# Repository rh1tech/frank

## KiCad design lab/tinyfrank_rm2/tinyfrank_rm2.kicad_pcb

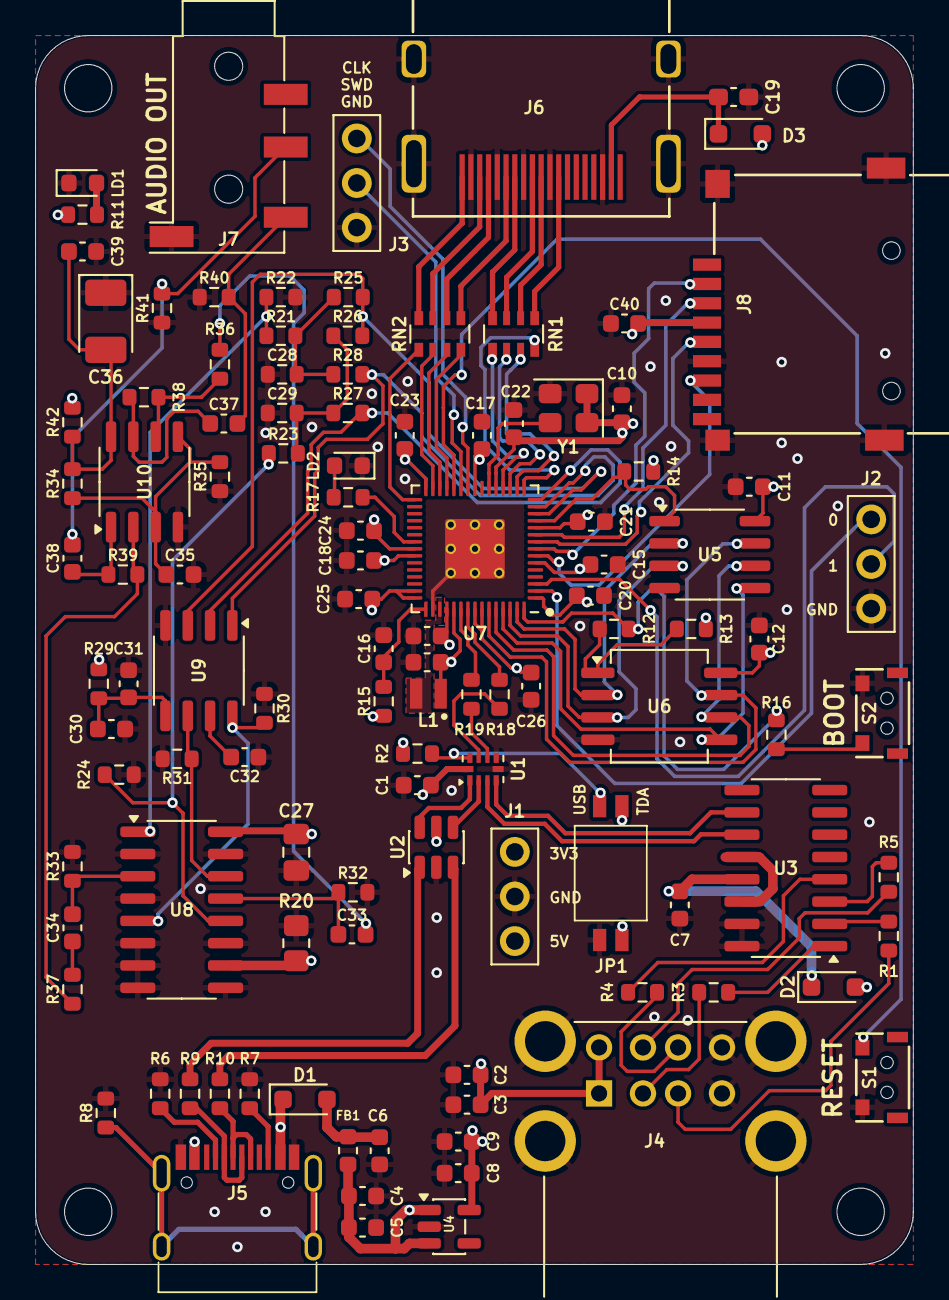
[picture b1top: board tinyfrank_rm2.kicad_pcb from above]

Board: 4 copper layers, 50.0 x 70.0 mm, 117 parts (0 on the bottom side), 97 nets.

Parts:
C1, C5, C6, C8, C10, C11, C12, C15, C18, C20, C21, C22, C23, C24, C25, C26, C31, C39, C40: 100n; C_0603_1608Metric
C2, C3, C4, C9, C30, C32, C33, C34, C35, C37, C38: 10u; C_0603_1608Metric
C7, C13, C14, C16, C17: 4.7u; C_0603_1608Metric
C19: 100n; Capacitor (0603)
C27: 100n; Capacitor (0805)
C28, C29: 47n; R_0603_1608Metric
C36: 10u; Capacitor (3528, tantalum, polar)
D1, D2, D3: 1N5819WS; Diode (SOD-323)
FB1: 330R; L_0603_1608Metric
H1, H2, H3, H4: Hole 2.7mm; Mounting Hole (2.7mm)
J1: PWR; Pin Header (1x03)
J2: UART; Pin Header (1x03)
J3: DEBUG; Pin Header (1x03)
J4: SS-52100-004; USB Type A (stacked)
J5: USB4215-03-A; USB Type C
J6: DC3RX19JA2; HDMI (female)
J7: PJ-320D; Jack (3.5mm, PJ-320D)
J8: 104031-0811; MicroSD (SMD, long)
JP1: Main Jumpers; DS05127202BKSMTTR
L1: 3.3u; L_pol_2016
LD1: Green; LED_0603_1608Metric
LD2: Blue; LED_0603_1608Metric
R1, R3, R4, R5, R9, R10: 22R; R_0603_1608Metric
R2, R13, R14, R21, R23, R32, R33, R34, R35, R36, R37: 10K; R_0603_1608Metric
R6, R7: 5.1K; R_0603_1608Metric
R8: 1M; R_0603_1608Metric
R11, R16, R17, R27, R28: 1K; R_0603_1608Metric
R12: 0R; R_0603_1608Metric
R15: 33R; R_0603_1608Metric
R18, R19: 27R; R_0603_1608Metric
R20: 10K; Resistor (0805)
R22, R24, R25, R26: 2K; R_0603_1608Metric
R29, R42: 100R; R_0603_1608Metric
R30, R31: 470R; R_0603_1608Metric
R38, R39: 47K; R_0603_1608Metric
R40, R41: 20K; R_0603_1608Metric
RN1, RN2: 270R; Resistor Array (4x0603)
S1: Reset RP2530A; TACT-SIDE-4623
S2: TS-1233; TACT-SIDE-4623
U1: TS3USB221RSER; UQFN-10
U2: USBLC6-2SC6; SOT-23-6
U3: MW7211A; SOP-16
U4: ME6211C33M5; SOT-23-5
U5: ESP-PSRAM32; SO-8
U6: W25Q128JVS; SOIC-8
U7: RP2350; QFN 60 (RP2350A)
U8: 74HC4052D; SOP-16
U9: TDA1387T; SO-8
U10: LM358; SO-8
Y1: ASE-12MHz; Oscillator_SMD_Abracon_ASE-4Pin_3.2x2.5mm

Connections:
+1V1: C14.1, C15.1, C17.1, C18.1, L1.1, U7.6 (DVDD), U7.23 (DVDD), U7.39 (DVDD), U7.50 (VREG_FB)
+3V3: C1.2, C8.1, C9.1, C10.1, C11.1, C12.1, C13.1, C20.1, C21.1, C22.1, C23.1, C24.1, C25.1, C26.1, C27.2, C40.2, J1.1, J8.4 (VDD), R2.1, R11.2, R13.1, R14.2, R15.1, U1.10 (VCC), U4.5 (V_{OUT}), U5.8 (VCC), U6.8 (VCC), U7.1 (IOVDD), U7.11 (IOVDD), U7.20 (IOVDD), U7.30 (IOVDD), U7.38 (IOVDD), U7.44 (ADC_AVDD), U7.45 (IOVDD), U7.49 (VREG_VIN), U7.53 (USB_OTP_VDD), U7.54 (QSPI_IOVDD), U8.16 (VCC), Y1.1 (EN), Y1.4 (Vdd)
/AMP_L: C33.1, R32.1, U8.13 (1Z)
/AMP_OUT_L: C37.2, J7.T, R40.2
/AMP_OUT_R: C38.2, J7.R, R41.2
/AMP_R: C34.1, R33.1, U8.3 (2Z)
/AUDIOSW: JP1.1, R20.2, U8.10 (S0)
/D+: R18.1, U1.8 (D+)
/D-: R19.1, U1.7 (D-)
/GPIO0: J2.1, U7.2 (GPIO0)
/GPIO1: J2.2, U7.3 (GPIO1)
/GPIO4: J8.7 (DAT0), U7.7 (GPIO4)
/GPIO5: J8.2 (DAT3/CD), U7.8 (GPIO5)
/GPIO6: J8.5 (CLK), U7.9 (GPIO6)
/GPIO7: J8.3 (CMD), U7.10 (GPIO7)
/GPIO8: R14.1, U5.1 (~CE), U7.12 (GPIO8)
/GPIO9: R25.1, R26.1, U7.13 (GPIO9), U9.3 (DATA)
/GPIO10: R28.2, U7.14 (GPIO10), U9.1 (SCLK)
/GPIO11: R27.2, U7.15 (GPIO11), U9.2 (LRCK)
/GPIO12: RN1.4 (R4.1), U7.16 (GPIO12)
/GPIO13: RN1.3 (R3.1), U7.17 (GPIO13)
/GPIO14: RN1.2 (R2.1), U7.18 (GPIO14)
/GPIO15: RN1.1 (R1.1), U7.19 (GPIO15)
/GPIO16: RN2.4 (R4.1), U7.27 (GPIO16)
/GPIO17: RN2.3 (R3.1), U7.28 (GPIO17)
/GPIO18: RN2.2 (R2.1), U7.29 (GPIO18)
/GPIO19: RN2.1 (R1.1), U7.31 (GPIO19)
/PWM_OUT_L: R23.2, R24.1, U8.12 (1Y0)
/PWM_OUT_R: R21.2, R22.1, U8.1 (2Y0)
/Power/D1+: U1.2 (1D-), U2.4 (I/O2)
/Power/D1-: U1.1 (1D+), U2.6 (I/O1)
/Power/D2+: U1.3 (2D+), U3.11 (DPU)
/Power/D2-: U1.4 (2D-), U3.10 (DMU)
/Power/DS1+: R1.1, U3.2 (DP0)
/Power/DS1-: R3.1, U3.1 (DM0)
/Power/DS2+: R4.1, U3.4 (DP1)
/Power/DS2-: R5.1, U3.3 (DM1)
/Power/VBUS_IN: C6.1, D1.2 (A), FB1.2
/RP2350A/FLASH_SS: R12.2, R13.2, U6.1 (~CS)
/RP2350A/QSPI_SCLK: U5.6 (SCLK), U6.6 (CLK), U7.56 (QSPI_SCLK)
/RP2350A/QSPI_SD0: U5.5 (SI/SIO), U6.5 (DI(IO0)), U7.57 (QSPI_SD0)
/RP2350A/QSPI_SD1: U5.2 (SO/SIO), U6.2 (DO(IO1)), U7.59 (QSPI_SD1)
/RP2350A/QSPI_SD2: U5.3 (SIO2), U6.3 (IO2), U7.58 (QSPI_SD2)
/RP2350A/QSPI_SD3: U5.7 (SIO3), U6.7 (IO3), U7.55 (QSPI_SD3)
/RP2350A/QSPI_SS: R12.1, R16.1, U7.60 (QSPI_SS)
/RP2350A/VREG_AVDD: C16.1, R15.2, U7.46 (VREG_AVDD)
/RP2350A/VREG_LX: L1.2, U7.48 (VREG_LX)
/RP2350A/XIN: U7.21 (XIN), Y1.3 (OUT)
/RP2350A/~USB_BOOT: R16.2, S2.2
/RUN: S1.1, U7.26 (RUN)
/SWCLK: J3.1, U7.24 (SWCLK)
/SWD: J3.2, U7.25 (SWD)
/TDA_L: R31.2, U8.14 (1Y1), U9.6 (A_LEFT)
/TDA_R: R30.1, U8.5 (2Y1), U9.8 (A_RIGHT)
/USBSW: JP1.2, R2.2, U1.9 (S)
GND: C1.1, C2.2, C3.2, C4.1, C5.1, C6.2, C7.2, C8.2, C9.2, C10.2, C11.2, C12.2, C13.2, C14.2, C15.2, C16.2, C17.2, C18.2, C19.2, C20.2, C21.2, C22.2, C23.2, C24.2, C25.2, C26.2, C27.1, C28.2, C29.2, C30.2, C31.2, C32.2, C35.1, C36.1, C39.1, C40.1, J1.2, J2.3, J3.3, J4.4 (GND1), J4.8 (GND2), J4.9 (Shield), J5.1 (GND), J5.12 (GND), J6.2 (G_D2), J6.5 (G_D1), J6.8 (G_D0), J6.11 (G_CLK), J6.17 (G_DDC/CEC), J6.20 (SHIELD1), J6.21 (SHIELD2), J6.22 (SHIELD3), J6.23 (SHIELD4), J7.S, J8.6 (VSS), JP1.3, LD1.1 (K), LD2.1 (K), R6.1, R7.1, R8.2, R20.1, R22.2, R24.2, R30.2, R31.1, R32.2, R33.2, R35.1, R40.1, R41.1, S1.2, S2.1, U1.5 (GND), U1.6 (~OE), U2.2 (GND), U3.15 (GND), U3.16 (GND), U4.2 (V_{SS}), U5.4 (VSS), U6.4 (GND), U7.47 (VREG_PGND), U7.61 (GND), U8.2 (2Y2), U8.4 (2Y3), U8.6 (~E), U8.7 (VEE), U8.8 (GND), U8.9 (S1), U8.11 (1Y3), U8.15 (1Y2), U9.4 (AGND), U10.4 (V-), Y1.2 (GND)
GPIO25: R17.2, U7.37 (GPIO25)
unnamed: C28.1, R21.1, R25.2, R28.1
unnamed: C29.1, R23.1, R26.2, R27.1
unnamed: C33.2, R36.2
unnamed: C34.2, R37.2
unnamed: C37.1, R38.1, U10.7
unnamed: C38.1, R39.1, U10.1
unnamed: D1.1 (K), J5.2 (VBUS), J5.11 (VBUS)
unnamed: C7.1, D2.1 (K), U3.13 (VDD5)
unnamed: C19.1, D3.1 (K), J6.18 (+5V)
unnamed: J4.3 (D1+), R1.2
unnamed: J4.2 (D1-), R3.2
unnamed: J4.7 (D2+), R4.2
unnamed: J4.6 (D2-), R5.2
unnamed: J5.4 (CC1), R6.2
unnamed: J5.10 (CC2), R7.2
unnamed: J5.5 (DN2), J5.7 (DN1), R9.2
unnamed: J5.6 (DP1), J5.8 (DP2), R10.2
unnamed: J5.13 (SHIELD), R8.1
unnamed: J6.12 (CLKN), RN1.5 (R4.2)
unnamed: J6.10 (CLKP), RN1.6 (R3.2)
unnamed: J6.9 (D0N), RN1.7 (R2.2)
unnamed: J6.7 (D0P), RN1.8 (R1.2)
unnamed: J6.6 (D1N), RN2.5 (R4.2)
unnamed: J6.4 (D1P), RN2.6 (R3.2)
unnamed: J6.3 (D2N), RN2.7 (R2.2)
unnamed: J6.1 (D2P), RN2.8 (R1.2)
unnamed: LD1.2 (A), R11.1
unnamed: LD2.2 (A), R17.1
unnamed: R9.1, U2.1 (I/O1)
unnamed: R10.1, U2.3 (I/O2)
unnamed: U3.12 (VD33), U3.14 (VD3)
unnamed: R19.2, U7.51 (USB_DM)
unnamed: R18.2, U7.52 (USB_DP)
unnamed: C32.1, U9.7 (FLT)
unnamed: C30.1, C31.1, R29.1, U9.5 (VA)
unnamed: C35.2, R34.1, R35.2, U10.3 (+), U10.5 (+)
unnamed: R37.1, R39.2, U10.2 (-)
unnamed: R36.1, R38.2, U10.6 (-)
unnamed: C36.2, C39.2, R34.2, R42.2, U10.8 (V+)
VBUS: C2.1, C3.1, C4.2, C5.2, D2.2 (A), D3.2 (A), FB1.1, J1.3, J4.1 (VBUS1), J4.5 (VBUS2), JP1.4, R29.2, R42.1, U2.5 (VBUS), U4.1 (V_{IN}), U4.3 (CE)

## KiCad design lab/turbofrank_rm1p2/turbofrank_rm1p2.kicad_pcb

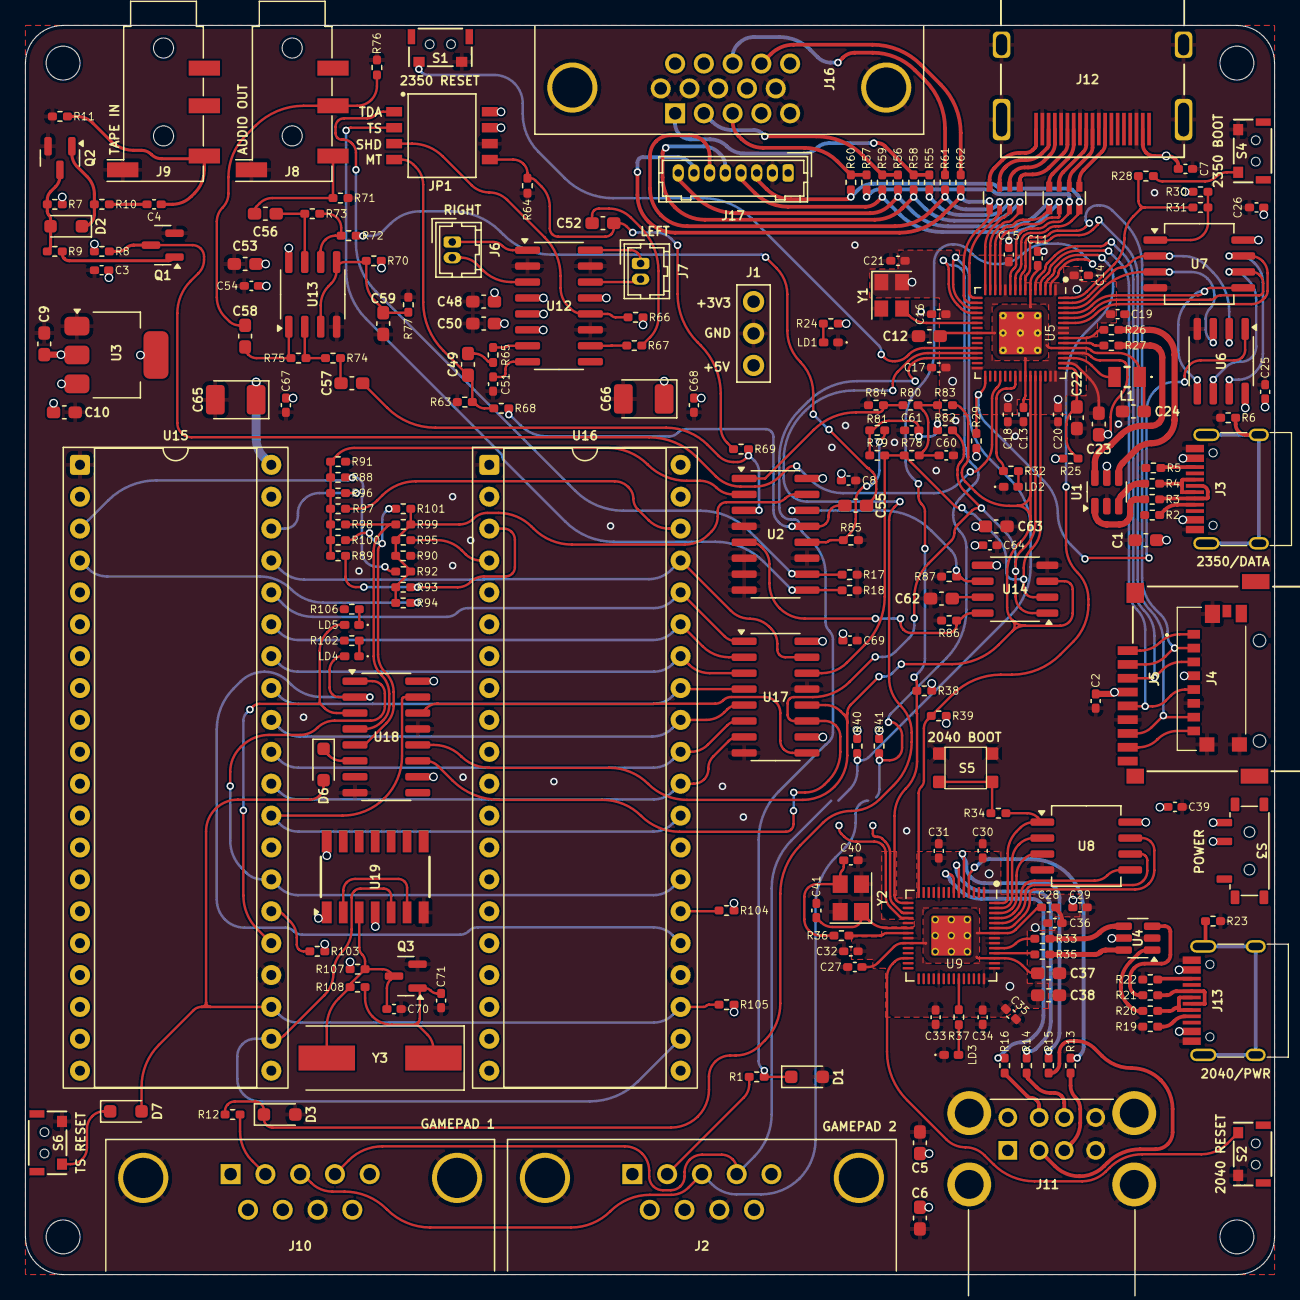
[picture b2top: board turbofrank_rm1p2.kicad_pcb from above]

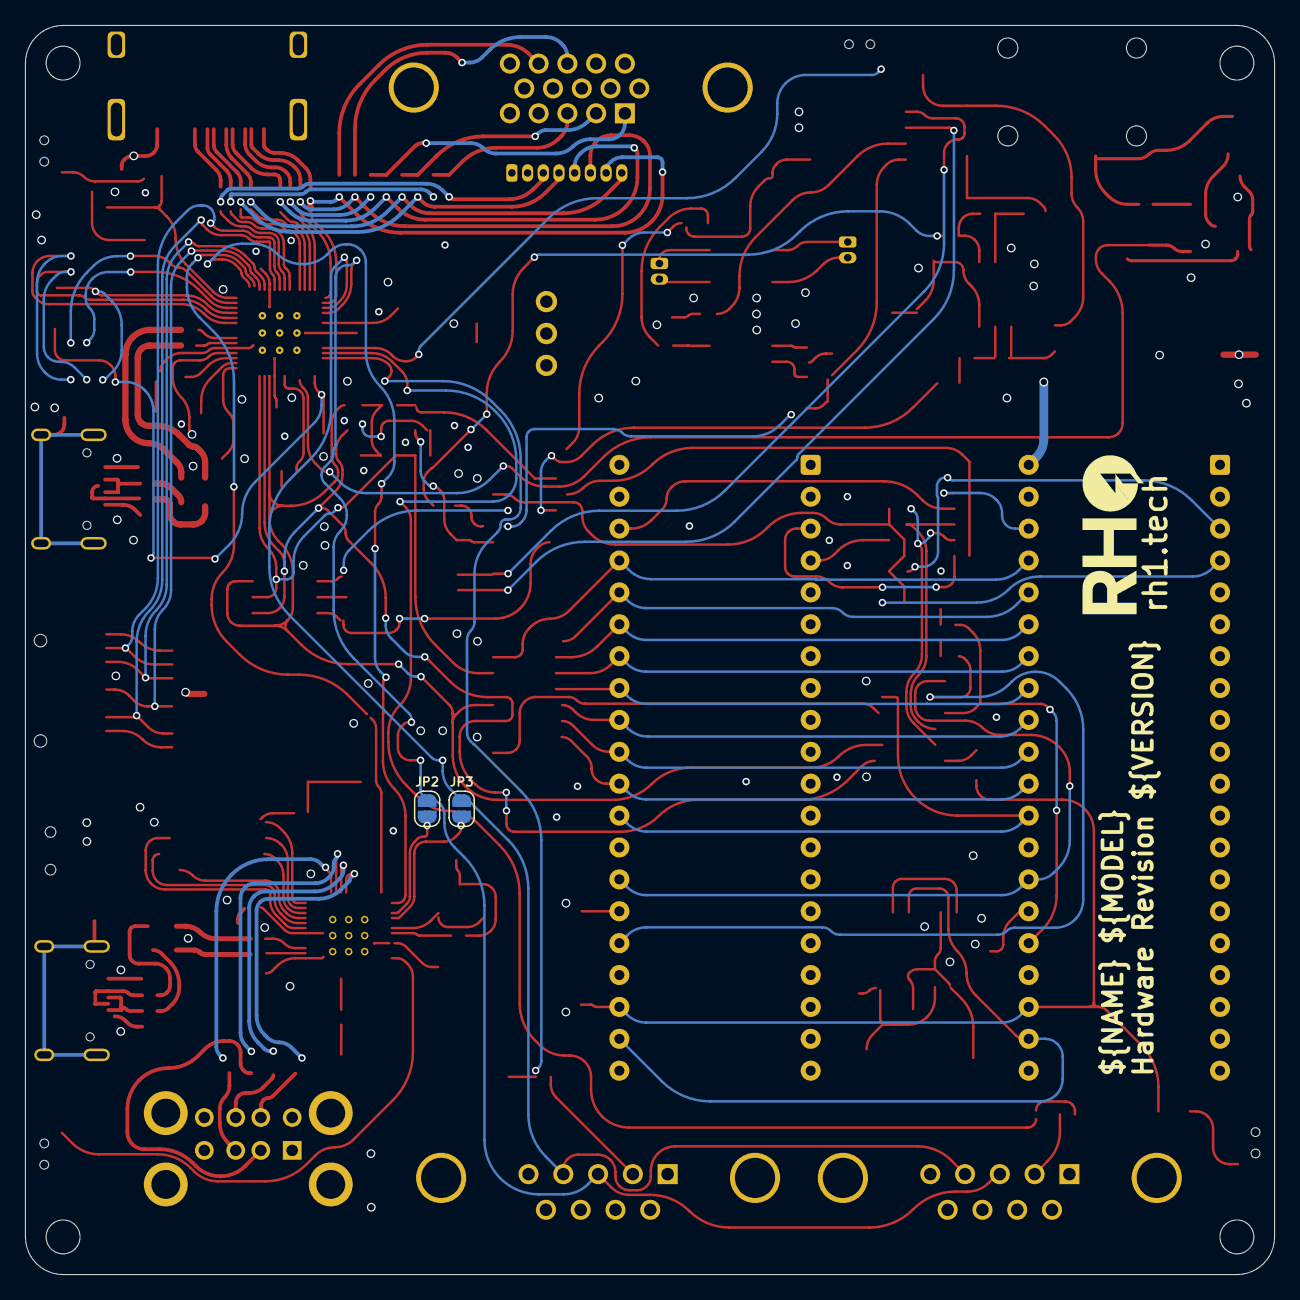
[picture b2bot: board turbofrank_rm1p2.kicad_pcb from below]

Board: 4 copper layers, 99.5 x 99.5 mm, 224 parts (2 on the bottom side), 177 nets.

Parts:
C1, C5, C6, C9, C10, C53, C55, C56, C57, C58, C59, C62, C63: 10u; Capacitor (0603)
C2, C3, C4, C7, C8, C11, C13, C14, C15, C16, C17, C18, C19, C20, C21, C25, C26, C27, C28, C29, C30, C31, C32, C33, C34, C35, C36, C39, C51, C54, C64, C67, C68, C69: 100n; Capacitor (0402)
C12, C22, C23, C24: 4.7u; Capacitor (0603)
C37, C38, C48, C49, C52: 1u; Capacitor (0603)
C40, C41: 15p; Capacitor (0402)
C50: 47u; Capacitor (0603)
C60, C61: 47n; Capacitor (0402)
C65, C66: 100u; Capacitor (3528, tantalum, polar)
C70, C71: 22p; Capacitor (0402)
D1, D3: 3V3; Diode (SOD-323)
D2, D6, D7: 1N4148; Diode (SOD-323)
H1, H2, H3, H4: MountingHole; Mounting Hole (2.7mm)
J1: PWR; Pin Header (1x03)
J2, J10: D-SUB 9 Male; D-SUB (9 pin, male, top mount)
J3, J13: USB4215-03-A; USB Type C
J4: 0475710001; MicroSD (SMD, short)
J5: 104031-0811; MicroSD (SMD, long)
J6: PAM L; Connector Female 1.25 JST 2P
J7: PAM R; Connector Female 1.25 JST 2P
J8, J9: PJ-320D; Jack (3.5mm, PJ-320D)
J11: SS-52100-004; USB Type A (stacked)
J12: DC3RX19JA2; HDMI (female)
J16: D-SUB 15 Female; D-SUB (15 pin, female)
J17: Pin Header 1x08; Connector Female 1.25 JST 8P
JP1: Main Jumpers; SW_DS05-127-2-04BK-SMT-TR
JP2: Mouse (DATA); Jumper (solder)
JP3: Mouse (CLK); Jumper (solder)
L1: 3.3u; Inductor (0806)
LD1: Power; LED (0402)
LD2, LD3: Blue; LED (0402)
LD4, LD5: Orange; LED (0402)
Q1, Q2, Q3: BC850; SOT-23
R1, R8, R12, R24, R28, R32, R34, R36, R37, R58, R59, R60, R82, R83, R102, R103, R104, R106, R107: 1K; Resistor (0402)
R2, R5, R19, R22: 5.1K; Resistor (0402)
R3, R4, R13, R14, R15, R16, R20, R21: 22R; Resistor (0402)
R6, R23: 1M; Resistor (0402)
R7, R9, R10, R17, R18, R29, R30, R38, R39, R40, R41, R65, R66, R67, R68, R69, R70, R72, R74, R77, R80, R81, R98, R99, R100, R101, R105: 10K; Resistor (0402)
R11, R61, R62: 100R; Resistor (0402)
R25: 33R; Resistor (0402)
R26, R27, R33, R35: 27R; Resistor (0402)
R31: 0R; Resistor (0402)
R55, R56, R57: 330R; Resistor (0402)
R63, R64, R78, R79, R84, R85, R88, R89, R94, R95: 2K; Resistor (0402)
R71, R76: 20K; Resistor (0402)
R73, R75: 47K; Resistor (0402)
R86, R87: 470R; Resistor (0402)
R90, R91: 120R; Resistor (0402)
R92, R93, R96, R97: 4.7K; Resistor (0402)
R108: 100K; Resistor (0402)
RN1, RN2: 270R; Resistor Array (4x0603)
S1: Reset RP2530A; TACT-SIDE-4623
S2: Reset RP2040; TACT-SIDE-4623
S3: MSK12C02; Switch (MSK12C02)
S4: Boot 2350; TACT-SIDE-4623
S5: Boot 2040; Button (SMD, 3x3mm, 1-1)
S6: KLS7-TS3302; TACT-SIDE-4623
U1, U4: USBLC6-2SC6; SOT-23-6
U2: 74HC4052D; SOP-16
U3: NCP1117 3.3; SOT-223
U5: RP2350; QFN 60 (RP2350A)
U6: ESP-PSRAM32; SO-8
U7: W25Q128JVS; SOIC-8
U8: W25Q128JVSIQ; SOIC-8
U9: RP2040; QFN 56
U12: PAM8403D; SOP-16
U13: LM358; SO-8
U14: TDA1387T; SO-8
U15, U16: JFC95101; DIP-40 (Socket)
U17, U18: 74HC595; SOP-16
U19: 74HC74; 74HCT74D
Y1: ASE-12MHz; Crystal (3225, active)
Y2: 12 MHz; Crystal (3225)
Y3: 3.58 MHz; Crystal (HC49-S)

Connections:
+1V1: C11.1, C12.1, C13.1, C24.1, L1.1, U5.6 (DVDD), U5.23 (DVDD), U5.39 (DVDD), U5.50 (VREG_FB)
+3V3: C2.2, C3.1, C9.1, C14.1, C15.1, C16.1, C17.1, C18.1, C19.1, C20.1, C21.1, C23.1, C25.1, C26.1, C29.1, C30.1, C31.1, C32.1, C33.1, C34.1, C35.1, C36.1, C38.1, C39.1, J1.1, J4.P4 (VDD), J5.4 (VDD), R7.1, R8.1, R24.2, R25.1, R29.2, R30.1, R38.2, R39.2, R40.2, R41.2, U3.2 (VO), U5.1 (IOVDD), U5.11 (IOVDD), U5.20 (IOVDD), U5.30 (IOVDD), U5.38 (IOVDD), U5.44 (ADC_AVDD), U5.45 (IOVDD), U5.49 (VREG_VIN), U5.53 (USB_OTP_VDD), U5.54 (QSPI_IOVDD), U6.8 (VCC), U7.8 (VCC), U8.8 (VCC), U9.1 (IOVDD), U9.10 (IOVDD), U9.22 (IOVDD), U9.33 (IOVDD), U9.42 (IOVDD), U9.43 (ADC_AVDD), U9.44 (VREG_IN), U9.48 (USB_VDD), U9.49 (IOVDD), Y1.1 (EN), Y1.4 (Vdd)
/AMP_IN_L: C55.1, R68.1, U2.13 (1Z)
/AMP_IN_R: C57.1, R69.1, U2.3 (2Z)
/Audio Out/AMP_OUTL: C56.2, J8.T, R71.2
/Audio Out/AMP_OUTR: C58.2, J8.R, R76.2
/Audio Out/AMP_PAM_OUTL_M: J6.2, U12.3 (-OUTL)
/Audio Out/AMP_PAM_OUTL_P: J6.1, U12.1 (+OUT_L)
/Audio Out/AMP_PAM_OUTR_M: J7.2, U12.14 (-OUT_R)
/Audio Out/AMP_PAM_OUTR_P: J7.1, U12.16 (+OUT_R)
/Audio Out/TS/A1: R95.2, U16.4 (B)
/Audio Out/TS/A2: R94.2, U15.4 (B)
/Audio Out/TS/B1: R89.2, R93.2, U16.3 (A)
/Audio Out/TS/B2: R88.2, R92.2, U15.3 (A)
/Audio Out/TS/BEEP: R98.2, R99.2, U18.4 (QE)
/Audio Out/TS/C1: R97.2, U16.38 (C)
/Audio Out/TS/C2: R96.2, U15.38 (C)
/Audio Out/TS/CLK_1.75M: U15.22 (CLOCK), U16.22 (CLOCK), U19.5 (Q)
/Audio Out/TS/DA0: U15.37 (DA0), U16.37 (DA0), U17.15 (QA)
/Audio Out/TS/DA1: U15.36 (DA1), U16.36 (DA1), U17.1 (QB)
/Audio Out/TS/DA2: U15.35 (DA2), U16.35 (DA2), U17.2 (QC)
/Audio Out/TS/DA3: U15.34 (DA3), U16.34 (DA3), U17.3 (QD)
/Audio Out/TS/DA4: U15.33 (DA4), U16.33 (DA4), U17.4 (QE)
/Audio Out/TS/DA5: U15.32 (DA5), U16.32 (DA5), U17.5 (QF)
/Audio Out/TS/DA6: U15.31 (DA6), U16.31 (DA6), U17.6 (QG)
/Audio Out/TS/DA7: U15.30 (DA7), U16.30 (DA7), U17.7 (QH)
/Audio Out/TS/SAVE: R100.2, R101.2, U18.5 (QF)
/Audio Out/TS/YM_BC1: U15.29 (BC1), U16.29 (BC1), U18.15 (QA)
/Audio Out/TS/YM_BDIR: U15.27 (BDIR), U16.27 (BDIR), U18.1 (QB)
/Audio Out/TS/YM_CS1: LD4.2 (A), U16.25 (A8), U18.2 (QC)
/Audio Out/TS/YM_CS2: LD5.2 (A), U15.25 (A8), U18.3 (QD)
/Audio Out/TS/YM_RST: D6.2 (A), D7.2 (A), R105.1, U15.23 (~RESET), U16.23 (~RESET)
/Audio Out/TS/YM_SEL1: R104.2, U16.26 (~SEL)
/Audio Out/TS/YM_SEL2: R103.2, U15.26 (~SEL)
/D+: R26.1, U1.4 (I/O2)
/D-: R27.1, U1.6 (I/O1)
/DAT1: J4.P8 (DAT1), J5.8 (DAT1)
/DAT2: J4.P1 (DAT2), J5.1 (DAT2)
/GPIO0: R38.1, U5.2 (GPIO0), U9.15 (GPIO12)
/GPIO1: R39.1, U5.3 (GPIO1), U9.14 (GPIO11)
/GPIO2: J4.P5 (CLK), J5.5 (CLK), U5.4 (GPIO2)
/GPIO3: J4.P3 (CMD), J5.3 (CMD), U5.5 (GPIO3)
/GPIO4: J4.P7 (DAT0), J5.7 (DAT0), U5.7 (GPIO4)
/GPIO5: J4.P2 (CD/DAT3), J5.2 (DAT3/CD), U5.8 (GPIO5)
/GPIO6: J17.3, R60.1, RN1.4 (R4.1), U5.9 (GPIO6)
/GPIO7: R57.1, RN1.3 (R3.1), U5.10 (GPIO7)
/GPIO8: J17.4, R59.1, RN1.2 (R2.1), U5.12 (GPIO8)
/GPIO9: J17.8, R56.1, RN1.1 (R1.1), U5.13 (GPIO9)
/GPIO10: J17.5, R58.1, RN2.4 (R4.1), U5.14 (GPIO10)
/GPIO11: R55.1, RN2.3 (R3.1), U5.15 (GPIO11)
/GPIO12: J17.6, R61.2, RN2.2 (R2.1), U5.16 (GPIO12)
/GPIO13: J17.7, R62.2, RN2.1 (R1.1), U5.17 (GPIO13)
/GPIO14: J2.4, J10.4, JP3.2 (B), R40.1, U5.18 (GPIO14)
/GPIO15: J2.3, J10.3, JP2.2 (B), R41.1, U5.19 (GPIO15)
/GPIO16: D3.1 (K), R12.1, U5.27 (GPIO16)
/GPIO17: D1.1 (K), R1.1, U5.28 (GPIO17)
/GPIO19: R29.1, U5.31 (GPIO19), U6.1 (~CE)
/GPIO22: Q1.3 (C), R8.2, U5.34 (GPIO22)
/GPIO26: R83.2, U5.40 (GPIO26_ADC0), U14.3 (DATA), U17.12 (RCLK), U18.12 (RCLK)
/GPIO27: R82.2, U5.41 (GPIO27_ADC1), U14.1 (SCLK), U17.11 (SRCLK), U18.11 (SRCLK)
/GPIO28: R78.1, R79.1, U5.42 (GPIO28_ADC2), U14.2 (LRCK), U17.14 (SER)
/J_TDA: JP1.1, R17.2, U2.10 (S0)
/J_TS: JP1.2, R18.2, U2.9 (S1)
/MONO_L: C49.1, JP1.4, R63.1, R68.2
/MONO_R: C52.1, JP1.5, R64.1, R69.2
/MS_CLK: JP3.1 (A), U9.18 (GPIO15)
/MS_DATA: JP2.1 (A), U9.17 (GPIO14)
/PWM_OUT_L: R81.2, R85.1, U2.12 (1Y0)
/PWM_OUT_R: R80.2, R84.1, U2.1 (2Y0)
/RP2_D+: R33.1, U4.4 (I/O2)
/RP2_D-: R35.1, U4.6 (I/O1)
/RP2_GPIO2: R13.1, U9.4 (GPIO2)
/RP2_GPIO3: R15.1, U9.5 (GPIO3)
/RP2_GPIO4: R14.1, U9.6 (GPIO4)
/RP2_GPIO5: R16.1, U9.7 (GPIO5)
/RP2_RUN: S2.1, U9.26 (RUN)
/RP2040/GPIO25: R37.2, U9.37 (GPIO25)
/RP2040/QSPI_SCLK: U8.6 (CLK), U9.52 (QSPI_SCLK)
/RP2040/QSPI_SD0: U8.5 (DI(IO0)), U9.53 (QSPI_SD0)
/RP2040/QSPI_SD1: U8.2 (DO(IO1)), U9.55 (QSPI_SD1)
/RP2040/QSPI_SD2: U8.3 (IO2), U9.54 (QSPI_SD2)
/RP2040/QSPI_SD3: U8.7 (IO3), U9.51 (QSPI_SD3)
/RP2040/QSPI_SS: R34.1, U8.1 (~CS), U9.56 (QSPI_SS)
/RP2040/XIN: C41.1, U9.20 (XIN), Y2.1
/RP2040/XOUT: R36.1, U9.21 (XOUT)
/RP2350A/FLASH_SS: R30.2, R31.2, U7.1 (~CS)
/RP2350A/QSPI_SCLK: U5.56 (QSPI_SCLK), U6.6 (SCLK), U7.6 (CLK)
/RP2350A/QSPI_SD0: U5.57 (QSPI_SD0), U6.5 (SI/SIO), U7.5 (DI(IO0))
/RP2350A/QSPI_SD1: U5.59 (QSPI_SD1), U6.2 (SO/SIO), U7.2 (DO(IO1))
/RP2350A/QSPI_SD2: U5.58 (QSPI_SD2), U6.3 (SIO2), U7.3 (IO2)
/RP2350A/QSPI_SD3: U5.55 (QSPI_SD3), U6.7 (SIO3), U7.7 (IO3)
/RP2350A/QSPI_SS: R28.1, R31.1, U5.60 (QSPI_SS)
/RP2350A/VREG_AVDD: C22.1, R25.2, U5.46 (VREG_AVDD)
/RP2350A/VREG_LX: L1.2, U5.48 (VREG_LX)
/RP2350A/XIN: U5.21 (XIN), Y1.3 (OUT)
/RP2350A/~USB_BOOT: R28.2, S4.2
/RUN: S1.1, U5.26 (RUN)
/SHND: JP1.3, R66.2, U12.12 (SHND)
/TDA_L: R87.2, U2.14 (1Y1), U14.6 (A_LEFT)
/TDA_R: R86.1, U2.5 (2Y1), U14.8 (A_RIGHT)
/TS_L: R90.1, R92.1, R93.1, R94.1, R95.1, R99.1, R101.1, U2.15 (1Y2)
/TS_R: R88.1, R89.1, R91.1, R96.1, R97.1, R98.1, R100.1, U2.2 (2Y2)
GND: C1.2, C2.1, C3.2, C5.2, C6.2, C7.2, C8.1, C9.2, C10.2, C11.2, C12.2, C13.2, C14.2, C15.2, C16.2, C17.2, C18.2, C19.2, C20.2, C21.2, C22.2, C23.2, C24.2, C25.2, C26.2, C27.2, C28.2, C29.2, C30.2, C31.2, C32.2, C33.2, C34.2, C35.2, C36.2, C37.2, C38.2, C39.2, C40.2, C41.2, C48.2, C50.2, C51.2, C53.1, C54.1, C59.1, C60.2, C61.2, C62.2, C63.2, C64.2, C65.2, C66.2, C67.2, C68.2, C69.2, C70.1, C71.1, D1.2 (A), D3.2 (A), J1.2, J2.8, J3.1 (GND), J3.12 (GND), J4.G1 (GND_1), J4.G2 (GND_2), J4.G3 (GND_3), J4.P6 (VSS), J5.6 (VSS), J8.S, J9.S, J10.8, J11.4 (GND1), J11.8 (GND2), J11.9 (Shield), J12.2 (G_D2), J12.5 (G_D1), J12.8 (G_D0), J12.11 (G_CLK), J12.17 (G_DDC/CEC), J12.20 (SHIELD1), J12.21 (SHIELD2), J12.22 (SHIELD3), J12.23 (SHIELD4), J13.1 (GND), J13.12 (GND), J16.0, J16.5, J16.6, J16.7, J16.8, J16.10, J17.2, JP1.6, LD1.1 (K), LD2.1 (K), LD3.1 (K), Q1.2 (E), Q2.2 (E), Q3.2 (E), R2.1, R5.1, R6.2, R11.2, R17.1, R18.1, R19.1, R22.1, R23.2, R63.2, R64.2, R71.1, R76.1, R77.1, R84.2, R85.2, R86.2, R87.1, R90.2, R91.2, R102.1, R106.1, S1.2, S2.2, S4.1, S5.2, S6.2, U1.2 (GND), U2.4 (2Y3), U2.6 (~E), U2.7 (VEE), U2.8 (GND), U2.11 (1Y3), U3.1 (GND), U4.2 (GND), U5.47 (VREG_PGND), U5.61 (GND), U6.4 (VSS), U7.4 (GND), U8.4 (GND), U9.19 (TESTEN), U9.57 (GND), U12.2 (PGND), U12.11 (GND), U12.15 (PGND), U13.4 (V-), U14.4 (AGND), U15.1 (VSS), U15.24 (~A9), U16.1 (VSS), U16.24 (~A9), U17.8 (GND), U17.13 (~OE), U18.8 (GND), U18.13 (~OE), U19.7 (GND), Y1.2 (GND), Y2.2, Y2.4
GPIO25: R32.2, U5.37 (GPIO25)
unnamed: C4.1, J9.T, R11.1
unnamed: C4.2, R10.1
unnamed: C40.1, R36.2, Y2.3
unnamed: C49.2, R65.2
unnamed: C52.2, R67.2
unnamed: C55.2, R72.2
unnamed: C56.1, R73.1, U13.7
unnamed: C57.2, R74.2
unnamed: C58.1, R75.1, U13.1
unnamed: C60.1, R78.2, R80.1, R83.1
unnamed: C61.1, R79.2, R81.1, R82.1
unnamed: D2.2 (A), Q2.3 (C), R7.2, R9.1
unnamed: D2.1 (K), Q2.1 (B), R10.2
unnamed: D6.1 (K), U18.6 (QG)
unnamed: D7.1 (K), S6.1
unnamed: J2.2, R1.2
unnamed: J3.4 (CC1), R2.2
unnamed: J3.10 (CC2), R5.2
unnamed: J3.5 (DN2), J3.7 (DN1), R3.2
unnamed: J3.6 (DP1), J3.8 (DP2), R4.2
unnamed: J3.13 (SHIELD), R6.1
unnamed: J10.2, R12.2
unnamed: J11.3 (D1+), R13.2
unnamed: J11.2 (D1-), R15.2
unnamed: J11.7 (D2+), R14.2
unnamed: J11.6 (D2-), R16.2
unnamed: J12.12 (CLKN), RN1.5 (R4.2)
unnamed: J12.10 (CLKP), RN1.6 (R3.2)
unnamed: J12.9 (D0N), RN1.7 (R2.2)
unnamed: J12.7 (D0P), RN1.8 (R1.2)
unnamed: J12.6 (D1N), RN2.5 (R4.2)
unnamed: J12.4 (D1P), RN2.6 (R3.2)
unnamed: J12.3 (D2N), RN2.7 (R2.2)
unnamed: J12.1 (D2P), RN2.8 (R1.2)
unnamed: J13.4 (CC1), R19.2
unnamed: J13.10 (CC2), R22.2
unnamed: J13.5 (DN2), J13.7 (DN1), R20.2
unnamed: J13.6 (DP1), J13.8 (DP2), R21.2
unnamed: J13.13 (SHIELD), R23.1
unnamed: J16.1, R55.2, R58.2
unnamed: J16.2, R56.2, R59.2
unnamed: J16.3, R57.2, R60.2
unnamed: J16.13, R61.1
unnamed: J16.14, R62.1
unnamed: LD1.2 (A), R24.1
unnamed: LD2.2 (A), R32.1
unnamed: LD3.2 (A), R37.1
unnamed: LD4.1 (K), R102.2
unnamed: LD5.1 (K), R106.2
unnamed: Q1.1 (B), R9.2
unnamed: C71.2, Q3.1 (B), R108.1, Y3.1
unnamed: C70.2, Q3.3 (C), R107.1, R108.2, U19.3 (C), Y3.2
unnamed: R3.1, U1.1 (I/O1)
unnamed: R4.1, U1.3 (I/O2)
unnamed: R20.1, U4.1 (I/O1)
unnamed: R21.1, U4.3 (I/O2)
unnamed: R34.2, S5.1
unnamed: J13.2 (VBUS), J13.11 (VBUS), S3.2 (B)
unnamed: R27.2, U5.51 (USB_DM)
unnamed: R26.2, U5.52 (USB_DP)
unnamed: R35.2, U9.46 (USB_DM)
unnamed: R33.2, U9.47 (USB_DP)
unnamed: C27.1, C28.1, C37.1, U9.23 (DVDD), U9.45 (VREG_VOUT), U9.50 (DVDD)
unnamed: R65.1, U12.7 (INL)
unnamed: R67.1, U12.10 (INR)
unnamed: C51.1, U12.8 (VREF)
unnamed: C59.2, R70.1, R77.2, U13.3 (+), U13.5 (+)
unnamed: R74.1, R75.2, U13.2 (-)
unnamed: R72.1, R73.2, U13.6 (-)
unnamed: C62.1, U14.7 (FLT)
unnamed: U17.9 (QH'), U18.14 (SER)
unnamed: U19.2 (D), U19.6 (~Q)
VBUS: C1.1, C5.1, C6.1, C7.1, C8.2, C10.1, C48.1, C50.1, C53.2, C54.2, C63.1, C64.1, C65.1, C66.1, C67.1, C68.1, C69.1, J1.3, J2.6, J3.2 (VBUS), J3.11 (VBUS), J10.6, J11.1 (VBUS1), J11.5 (VBUS2), J12.18 (+5V), J17.1, JP1.7, JP1.8, R66.1, R70.2, R103.1, R104.1, R105.2, R107.2, S3.3 (A), U1.5 (VBUS), U2.16 (VCC), U3.3 (VI), U4.5 (VBUS), U12.4 (PVDD), U12.5 (MUTE), U12.6 (VDD), U12.13 (PVDD), U13.8 (V+), U14.5 (VA), U15.28 (BC2), U15.40 (VCC), U16.28 (BC2), U16.40 (VCC), U17.10 (~SRCLR), U17.16 (VCC), U18.10 (~SRCLR), U18.16 (VCC), U19.1 (~R), U19.4 (~S), U19.14 (VCC)

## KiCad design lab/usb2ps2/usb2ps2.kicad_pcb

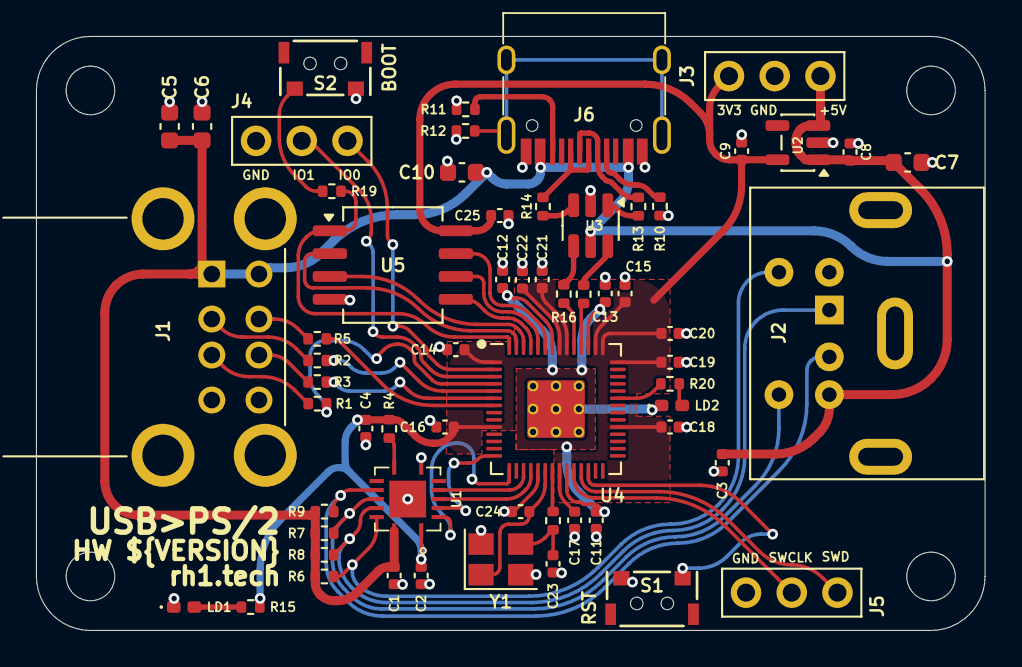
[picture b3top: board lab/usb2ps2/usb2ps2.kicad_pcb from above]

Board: 2 copper layers, 52.7 x 33.0 mm, 65 parts (0 on the bottom side), 50 nets.

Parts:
C1, C2, C3, C4, C11, C12, C14, C16, C17, C18, C19, C20, C21, C22, C25: 100n; Capacitor (0402, S)
C5, C6, C7, C10: 10u; Capacitor (0603, S)
C8, C9, C13, C15: 1u; Capacitor (0402, S)
C23, C24: 15p; Capacitor (0402, S)
H1, H2, H3, H4: MountingHole; Mounting Hole (2.7mm)
J1: SS-52100-004; USB Type A (stacked)
J2: MDC-036; MiniDIN (6 Pin, female)
J3: PWR; Pin Header (1x03)
J4: DEBUG; Pin Header (1x03)
J5: SW; Pin Header (1x03)
J6: USB4215-03-A; USB Type C
LD1: Green; LED (0402)
LD2: Blue; LED (0402)
R1, R2, R3, R5, R13, R14: 22R; Resistor (0402, S)
R4: 4.7K; Resistor (0402, S)
R6, R7, R8, R9: 10K; Resistor (0402, S)
R10, R11: 5.1K; Resistor (0402, S)
R12: 1M; Resistor (0402, S)
R15, R18, R19, R20: 1K; Resistor (0402, S)
R16, R17: 27R; Resistor (0402, S)
S1: Reset; TACT-SIDE-4623
S2: Boot; TACT-SIDE-4623
U1: TXS0104ERGYR; RGY_S-PVQFN-N14_
U2: ME6211C33M5; SOT-23-5
U3: USBLC6-2SC6; SOT-23-6
U4: RP2040; QFN 56
U5: W25Q128JVSIQ; SOIC-8
Y1: 12 MHz; Crystal (3225)

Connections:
+3V3: C2.2, C4.1, C9.1, C14.1, C15.1, C16.1, C17.1, C18.1, C19.1, C20.1, C21.1, C22.1, C25.1, J3.1, R4.2, R15.2, U1.1 (VCCA), U2.5 (V_{OUT}), U4.1 (IOVDD), U4.10 (IOVDD), U4.22 (IOVDD), U4.33 (IOVDD), U4.42 (IOVDD), U4.43 (ADC_AVDD), U4.44 (VREG_IN), U4.48 (USB_VDD), U4.49 (IOVDD), U5.8 (VCC)
/GPIO0: J4.3, U4.2 (GPIO0)
/GPIO1: J4.2, U4.3 (GPIO1)
/GPIO2: R1.1, U4.4 (GPIO2)
/GPIO3: R2.1, U4.5 (GPIO3)
/GPIO4: R3.1, U4.6 (GPIO4)
/GPIO5: R5.1, U4.7 (GPIO5)
/GPIO11: U1.3 (A2), U4.14 (GPIO11)
/GPIO12: U1.2 (A1), U4.15 (GPIO12)
/GPIO14: U1.5 (A4), U4.17 (GPIO14)
/GPIO15: U1.4 (A3), U4.18 (GPIO15)
/GPIO25: R20.2, U4.37 (GPIO25)
/KB_CLK_5V: J2.5, R6.1, U1.13 (B1)
/KB_DATA_5V: J2.1, R8.1, U1.12 (B2)
/MS_CLK_5V: J2.6, R7.1, U1.11 (B3)
/MS_DATA_5V: J2.2, R9.1, U1.10 (B4)
/PW_D+: R16.1, U3.4 (I/O2)
/PW_D-: R17.1, U3.6 (I/O1)
/RP2040/QSPI_SCLK: U4.52 (QSPI_SCLK), U5.6 (CLK)
/RP2040/QSPI_SD0: U4.53 (QSPI_SD0), U5.5 (DI(IO0))
/RP2040/QSPI_SD1: U4.55 (QSPI_SD1), U5.2 (DO(IO1))
/RP2040/QSPI_SD2: U4.54 (QSPI_SD2), U5.3 (IO2)
/RP2040/QSPI_SD3: U4.51 (QSPI_SD3), U5.7 (IO3)
/RP2040/QSPI_SS: R19.1, U4.56 (QSPI_SS), U5.1 (~CS)
/RP2040/XIN: C24.1, U4.20 (XIN), Y1.1
/RP2040/XOUT: R18.1, U4.21 (XOUT)
/RUN: S1.1, U4.26 (RUN)
/SWCLK: J5.2, U4.24 (SWCLK)
/SWD: J5.3, U4.25 (SWD)
GND: C1.2, C2.1, C3.2, C4.2, C5.2, C6.2, C7.1, C8.1, C9.2, C10.2, C11.2, C12.2, C13.2, C14.2, C15.2, C16.2, C17.2, C18.2, C19.2, C20.2, C21.2, C22.2, C23.2, C24.2, C25.2, J1.4 (GND1), J1.8 (GND2), J1.9 (Shield), J2.3, J3.2, J4.1, J5.1, J6.1 (GND), J6.12 (GND), LD1.1 (K), LD2.1 (K), R10.1, R11.1, R12.2, S1.2, S2.2, U1.7 (GND), U1.15 (THERMAL_PAD), U2.2 (V_{SS}), U3.2 (GND), U4.19 (TESTEN), U4.57 (GND), U5.4 (GND), Y1.2, Y1.4
unnamed: C23.1, R18.2, Y1.3
unnamed: J1.3 (D1+), R1.2
unnamed: J1.2 (D1-), R2.2
unnamed: J1.7 (D2+), R3.2
unnamed: J1.6 (D2-), R5.2
unnamed: J6.4 (CC1), R10.2
unnamed: J6.10 (CC2), R11.2
unnamed: J6.5 (DN2), J6.7 (DN1), R13.2
unnamed: J6.6 (DP1), J6.8 (DP2), R14.2
unnamed: J6.13 (SHIELD), R12.1
unnamed: LD1.2 (A), R15.1
unnamed: LD2.2 (A), R20.1
unnamed: R13.1, U3.1 (I/O1)
unnamed: R14.1, U3.3 (I/O2)
unnamed: R19.2, S2.1
unnamed: R4.1, U1.8 (OE)
unnamed: R17.2, U4.46 (USB_DM)
unnamed: R16.2, U4.47 (USB_DP)
unnamed: C11.1, C12.1, C13.1, U4.23 (DVDD), U4.45 (VREG_VOUT), U4.50 (DVDD)
VBUS: C1.1, C3.1, C5.1, C6.1, C7.2, C8.2, C10.1, J1.1 (VBUS1), J1.5 (VBUS2), J2.4, J3.3, J6.2 (VBUS), J6.11 (VBUS), R6.2, R7.2, R8.2, R9.2, U1.14 (VCCB), U2.1 (V_{IN}), U2.3 (CE), U3.5 (VBUS)

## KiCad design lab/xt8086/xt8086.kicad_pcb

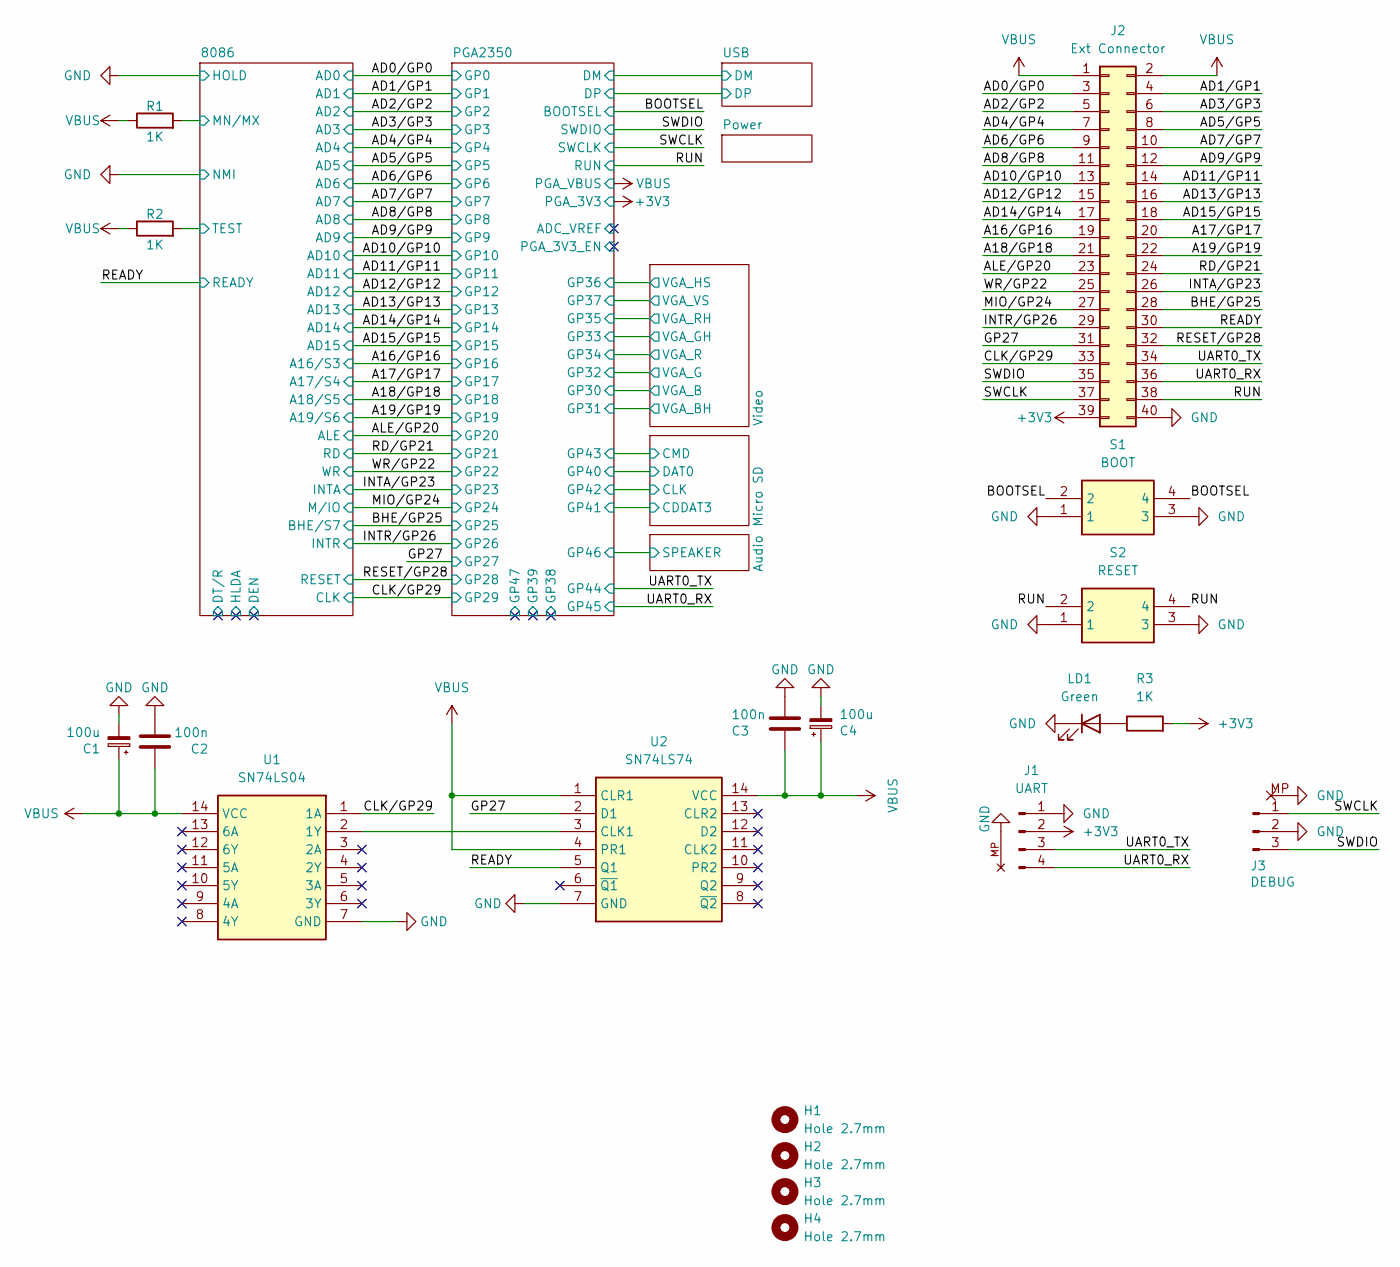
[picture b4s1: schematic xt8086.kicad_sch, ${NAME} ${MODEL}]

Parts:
C1, C4: 100u; CP_Radial_D6.3mm_P2.50mm
C2, C3: 100n; C_0805_2012Metric
H1, H2, H3, H4: Hole 2.7mm; MountingHole_2.7mm
J1: UART; JST_SH_1x04_P1.00mm_Vertical
J2: Ext Connector; PinHeader_2x20_P2.54mm_Vertical
J3: DEBUG; JST_SH_1x03_P1.00mm_Vertical
LD1: Green; LED_0805_2012Metric_Pad1.15x1.40mm_HandSolder
R1, R2, R3: 1K; R_0805_2012Metric
S1: BOOT; Button_SMD_3x4x2mm; Mouser Part Number 611-KMR221G-LFS
S2: RESET; Button_SMD_3x4x2mm; Mouser Part Number 611-KMR221G-LFS
U1: SN74LS04; DIP-14_W7.62mm; Mouser Part Number 595-SN74LS04N
U2: SN74LS74; DIP-14_W7.62mm; Mouser Part Number 595-SN74LS74ANE4

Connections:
+3V3: J1.2, J2.39, R3.2; also elsewhere on the board
/8086/MN/MX: R1.2; also elsewhere on the board
/8086/TEST: R2.2; also elsewhere on the board
/A16/GP16: J2.19; also elsewhere on the board
/A17/GP17: J2.20; also elsewhere on the board
/A18/GP18: J2.21; also elsewhere on the board
/A19/GP19: J2.22; also elsewhere on the board
/AD0/GP0: J2.3; also elsewhere on the board
/AD1/GP1: J2.4; also elsewhere on the board
/AD2/GP2: J2.5; also elsewhere on the board
/AD3/GP3: J2.6; also elsewhere on the board
/AD4/GP4: J2.7; also elsewhere on the board
/AD5/GP5: J2.8; also elsewhere on the board
/AD6/GP6: J2.9; also elsewhere on the board
/AD7/GP7: J2.10; also elsewhere on the board
/AD8/GP8: J2.11; also elsewhere on the board
/AD9/GP9: J2.12; also elsewhere on the board
/AD10/GP10: J2.13; also elsewhere on the board
/AD11/GP11: J2.14; also elsewhere on the board
/AD12/GP12: J2.15; also elsewhere on the board
/AD13/GP13: J2.16; also elsewhere on the board
/AD14/GP14: J2.17; also elsewhere on the board
/AD15/GP15: J2.18; also elsewhere on the board
/ALE/GP20: J2.23; also elsewhere on the board
/BOOTSEL: S1.2, S1.4; also elsewhere on the board
/CLK/GP29: J2.33, U1.1 (1A); also elsewhere on the board
/GP27: J2.31, U2.2 (D1); also elsewhere on the board
/INTA/GP23: J2.26; also elsewhere on the board
/INTR/GP26: J2.29; also elsewhere on the board
/MIO/GP24: J2.27; also elsewhere on the board
/RD/GP21: J2.24; also elsewhere on the board
/READY: J2.30, U2.5 (Q1); also elsewhere on the board
/RESET/GP28: J2.32; also elsewhere on the board
/RUN: J2.38, S2.2, S2.4; also elsewhere on the board
/SWCLK: J2.37, J3.1; also elsewhere on the board
/SWDIO: J2.35, J3.3; also elsewhere on the board
/UART0_RX: J1.4, J2.36; also elsewhere on the board
/UART0_TX: J1.3, J2.34; also elsewhere on the board
/WR/GP22: J2.25; also elsewhere on the board
GND: C1.2, C2.2, C3.2, C4.2, J1.1, J1.MP, J2.40, J3.2, J3.MP, LD1.1 (K), S1.1, S1.3, S2.1, S2.3, U1.7 (GND), U2.7 (GND); also elsewhere on the board
GP25: J2.28; also elsewhere on the board
unnamed: LD1.2 (A), R3.1
unnamed: U1.2 (1Y), U2.3 (CLK1)
VBUS: C1.1, C2.1, C3.1, C4.1, J2.1, J2.2, R1.1, R2.1, U1.14 (VCC), U2.1 (CLR1), U2.4 (PR1), U2.14 (VCC); also elsewhere on the board
